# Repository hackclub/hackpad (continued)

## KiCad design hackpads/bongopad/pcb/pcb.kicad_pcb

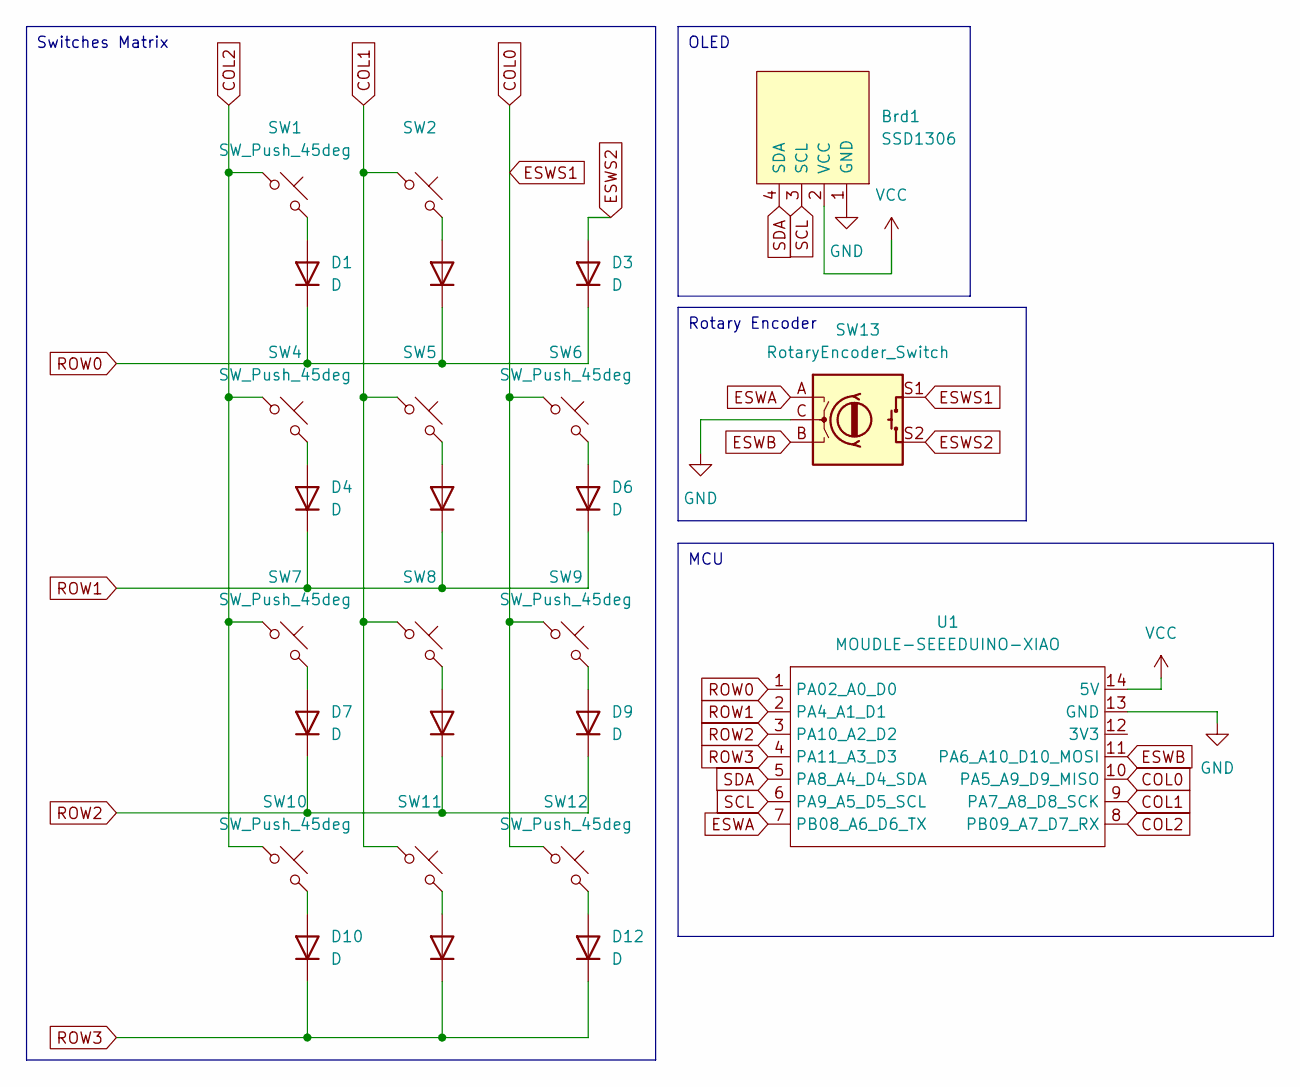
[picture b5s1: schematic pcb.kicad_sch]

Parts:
Brd1: SSD1306; 128x64OLED
D1, D2, D3, D4, D5, D6, D7, D8, D9, D10, D11, D12: D; D_DO-35_SOD27_P7.62mm_Horizontal
SW1, SW2, SW4, SW5, SW6, SW7, SW8, SW9, SW10, SW11, SW12: SW_Push_45deg; MX-Solderable-1U
SW13: RotaryEncoder_Switch; RotaryEncoder_Alps_EC11E-Switch_Vertical_H20mm
U1: MOUDLE-SEEEDUINO-XIAO; XIAO-Generic-Hybrid-14P-2.54-21X17.8MM

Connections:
COL0: SW6.1, SW9.1, SW12.1, SW13.S1, U1.10 (PA5_A9_D9_MISO)
COL1: SW2.1, SW5.1, SW8.1, SW11.1, U1.9 (PA7_A8_D8_SCK)
COL2: SW1.1, SW4.1, SW7.1, SW10.1, U1.8 (PB09_A7_D7_RX)
ESWA: SW13.A, U1.7 (PB08_A6_D6_TX)
ESWB: SW13.B, U1.11 (PA6_A10_D10_MOSI)
ESWS2: D3.2 (A), SW13.S2
GND: Brd1.1 (GND), SW13.C, U1.13 (GND)
unnamed: D1.2 (A), SW1.2
unnamed: D2.2 (A), SW2.2
unnamed: D4.2 (A), SW4.2
unnamed: D5.2 (A), SW5.2
unnamed: D6.2 (A), SW6.2
unnamed: D7.2 (A), SW7.2
unnamed: D8.2 (A), SW8.2
unnamed: D9.2 (A), SW9.2
unnamed: D10.2 (A), SW10.2
unnamed: D11.2 (A), SW11.2
unnamed: D12.2 (A), SW12.2
ROW0: D1.1 (K), D2.1 (K), D3.1 (K), U1.1 (PA02_A0_D0)
ROW1: D4.1 (K), D5.1 (K), D6.1 (K), U1.2 (PA4_A1_D1)
ROW2: D7.1 (K), D8.1 (K), D9.1 (K), U1.3 (PA10_A2_D2)
ROW3: D10.1 (K), D11.1 (K), D12.1 (K), U1.4 (PA11_A3_D3)
SCL: Brd1.3 (SCL), U1.6 (PA9_A5_D5_SCL)
SDA: Brd1.4 (SDA), U1.5 (PA8_A4_D4_SDA)
VCC: Brd1.2 (VCC), U1.14 (5V)

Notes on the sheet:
MCU
Switches Matrix
OLED
Rotary Encoder

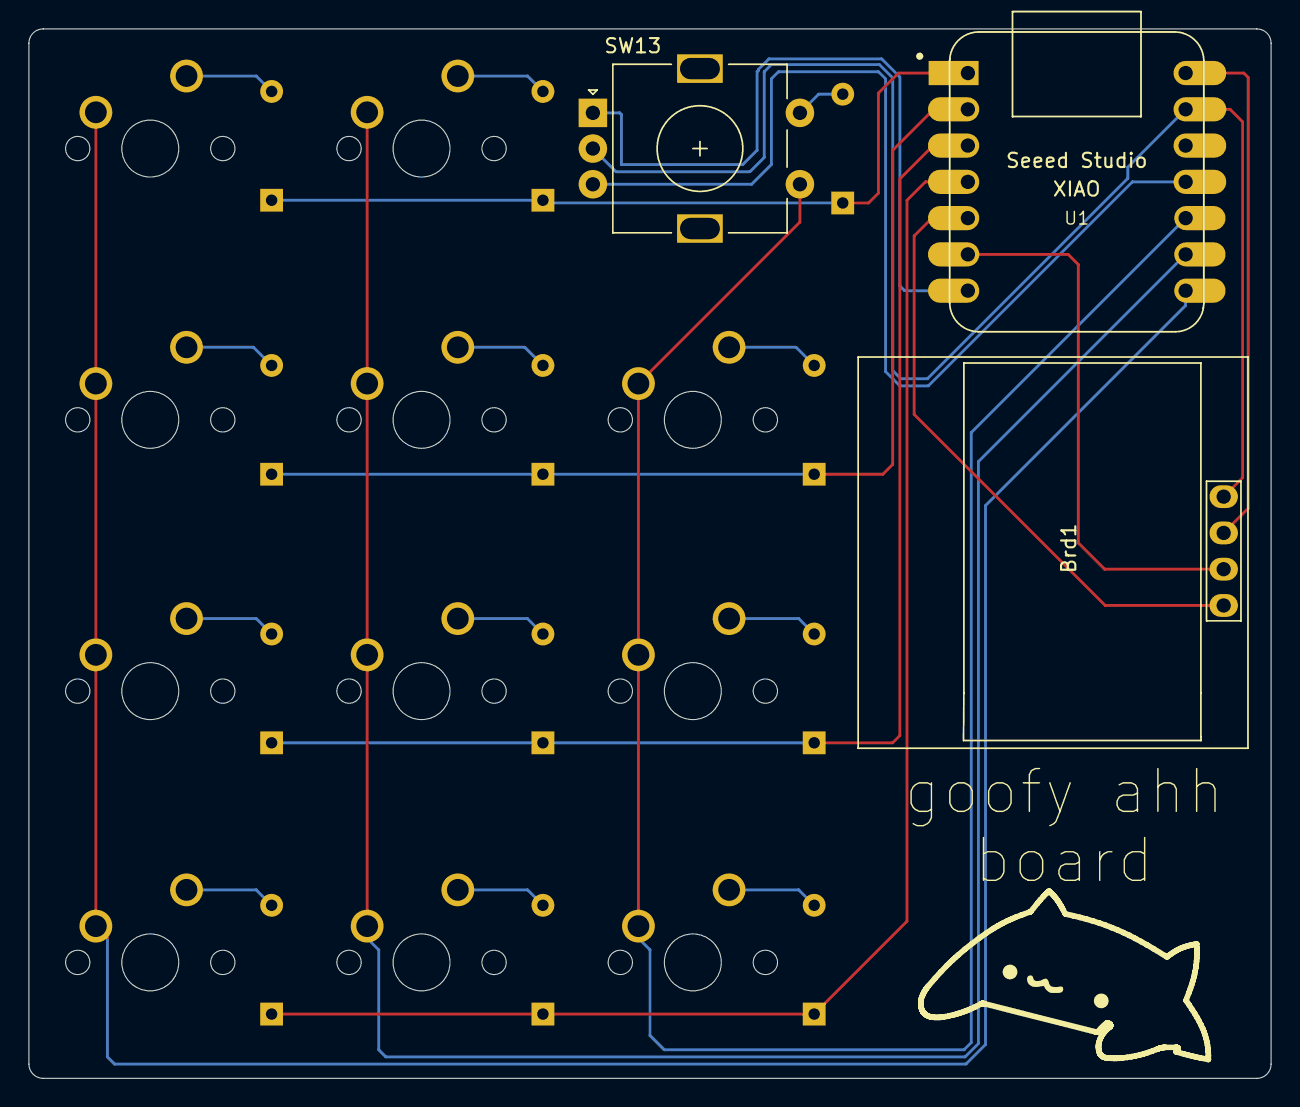
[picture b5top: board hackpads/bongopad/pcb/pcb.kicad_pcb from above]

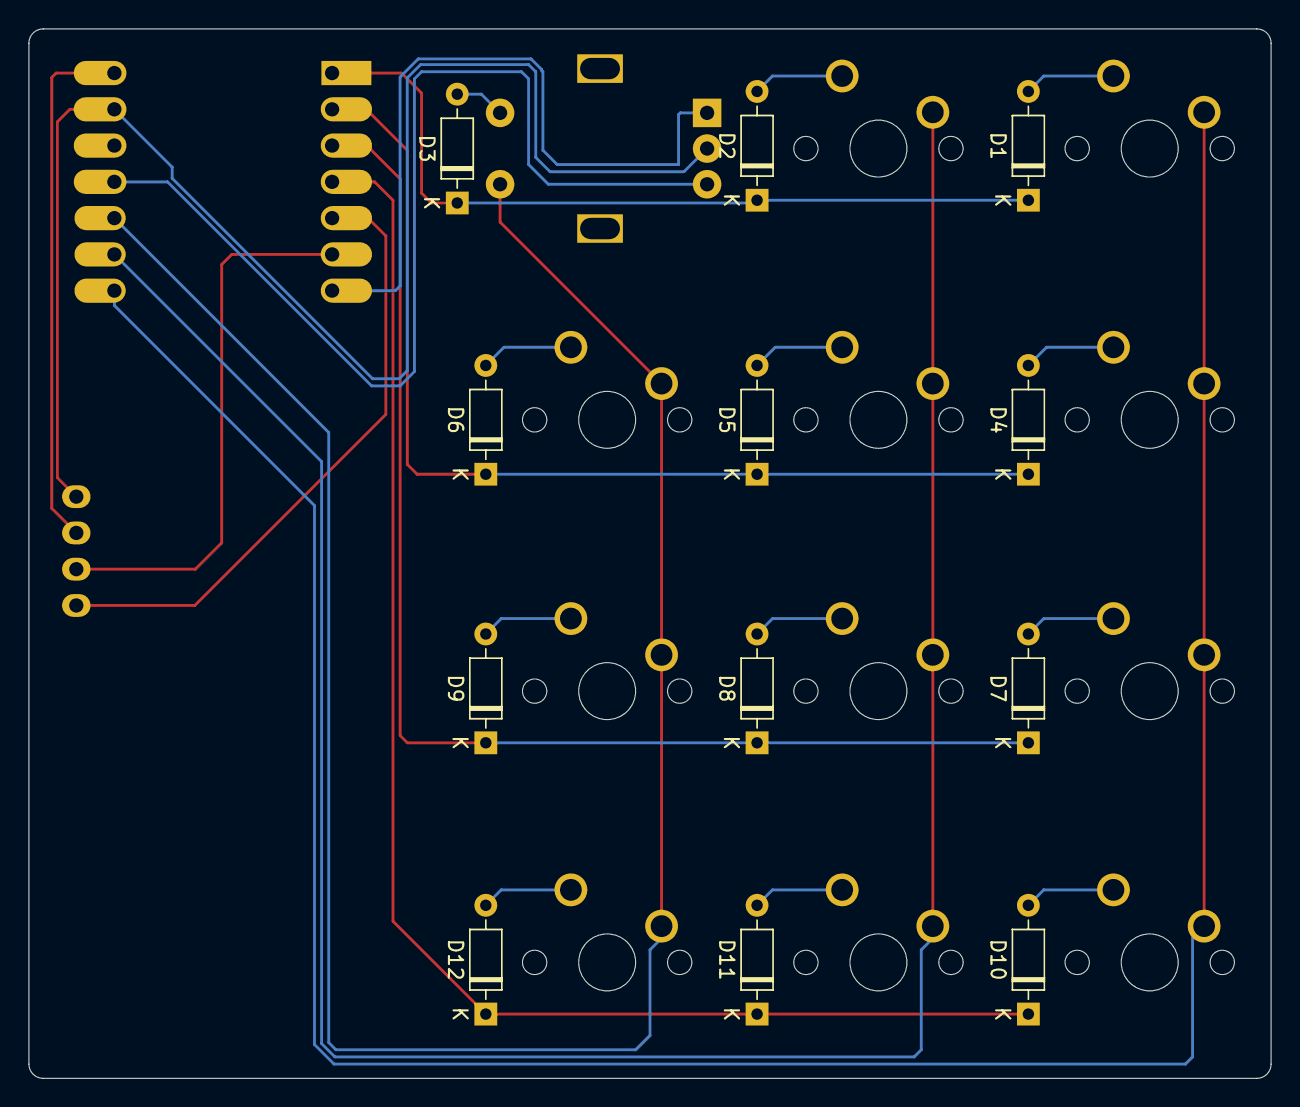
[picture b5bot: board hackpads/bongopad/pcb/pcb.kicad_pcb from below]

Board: 2 copper layers, 87.0 x 73.5 mm, 26 parts (12 on the bottom side), 25 nets.

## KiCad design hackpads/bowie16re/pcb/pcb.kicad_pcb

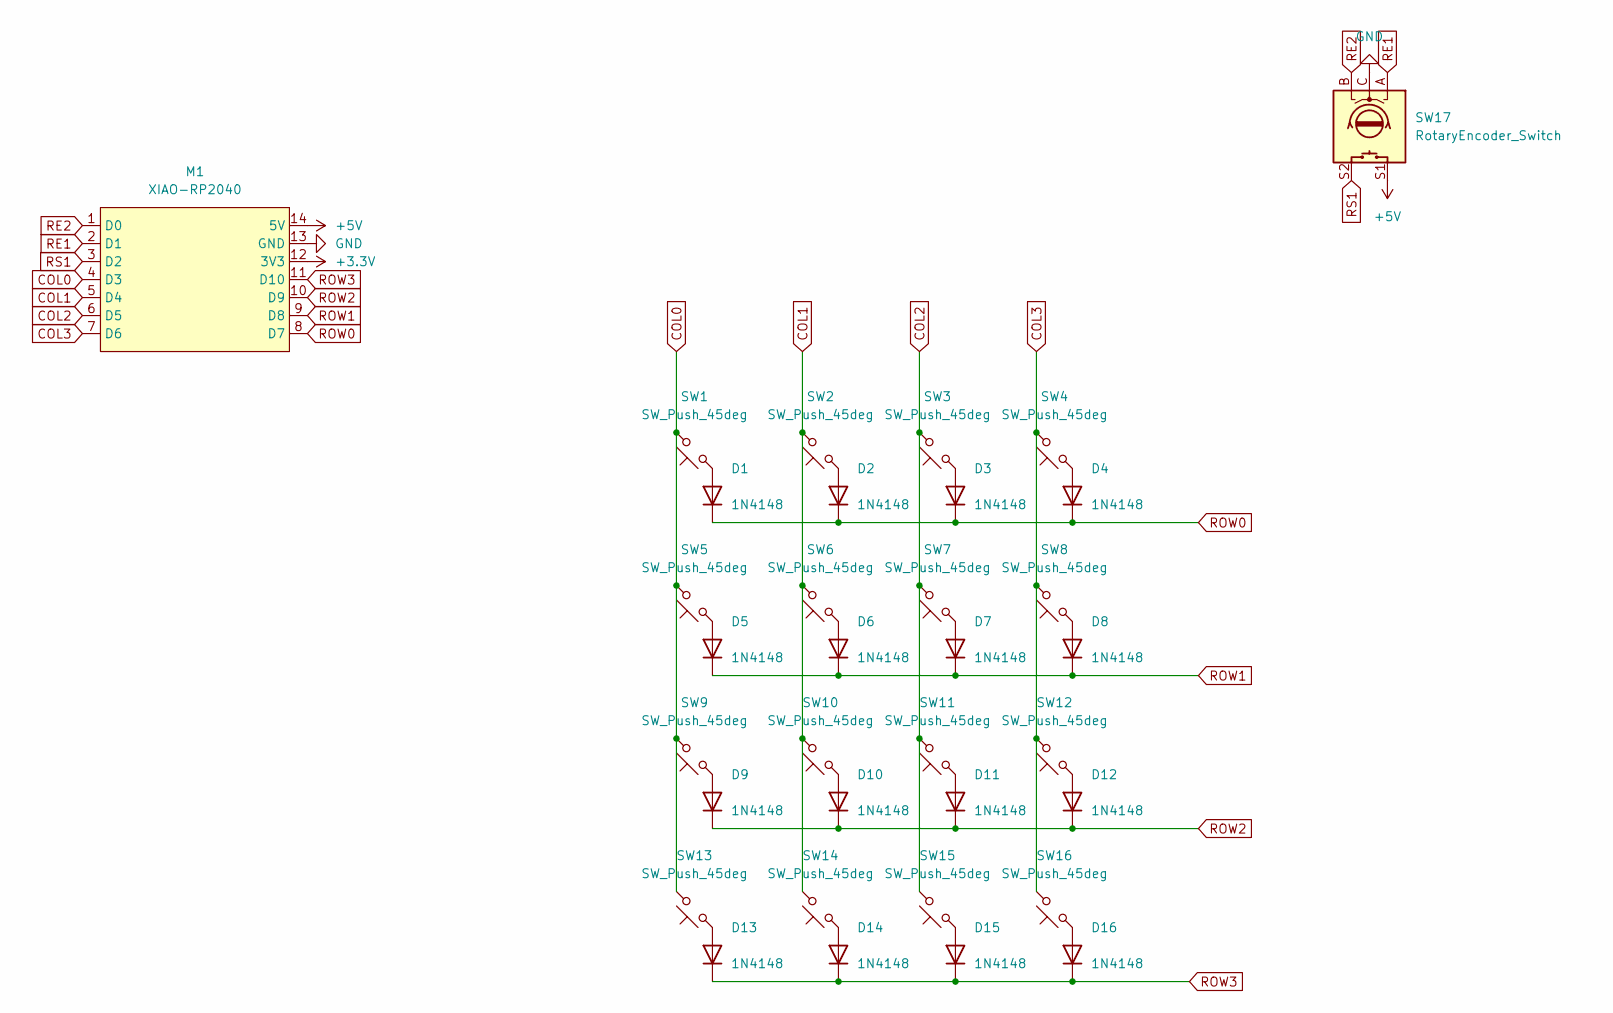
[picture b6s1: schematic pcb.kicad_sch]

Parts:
D1, D2, D3, D4, D5, D6, D7, D8, D9, D10, D11, D12, D13, D14, D15, D16: 1N4148; D_DO-35_SOD27_P7.62mm_Horizontal
M1: XIAO-RP2040
SW1, SW2, SW3, SW4, SW5, SW6, SW7, SW8, SW9, SW10, SW11, SW12, SW13, SW14, SW15, SW16: SW_Push_45deg; SW_Cherry_MX_1.00u_PCB
SW17: RotaryEncoder_Switch; RotaryEncoder_Alps_EC11E-Switch_Vertical_H20mm

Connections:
+3.3V: M1.12 (3V3)
+5V: M1.14 (5V), SW17.S1
COL0: M1.4 (D3), SW1.2, SW5.2, SW9.2, SW13.2
COL1: M1.5 (D4), SW2.2, SW6.2, SW10.2, SW14.2
COL2: M1.6 (D5), SW3.2, SW7.2, SW11.2, SW15.2
COL3: M1.7 (D6), SW4.2, SW8.2, SW12.2, SW16.2
GND: M1.13 (GND), SW17.C
unnamed: D1.2 (A), SW1.1
unnamed: D2.2 (A), SW2.1
unnamed: D3.2 (A), SW3.1
unnamed: D4.2 (A), SW4.1
unnamed: D5.2 (A), SW5.1
unnamed: D6.2 (A), SW6.1
unnamed: D7.2 (A), SW7.1
unnamed: D8.2 (A), SW8.1
unnamed: D9.2 (A), SW9.1
unnamed: D10.2 (A), SW10.1
unnamed: D11.2 (A), SW11.1
unnamed: D12.2 (A), SW12.1
unnamed: D13.2 (A), SW13.1
unnamed: D14.2 (A), SW14.1
unnamed: D15.2 (A), SW15.1
unnamed: D16.2 (A), SW16.1
RE1: M1.2 (D1), SW17.A
RE2: M1.1 (D0), SW17.B
ROW0: D1.1 (K), D2.1 (K), D3.1 (K), D4.1 (K), M1.8 (D7)
ROW1: D5.1 (K), D6.1 (K), D7.1 (K), D8.1 (K), M1.9 (D8)
ROW2: D9.1 (K), D10.1 (K), D11.1 (K), D12.1 (K), M1.10 (D9)
ROW3: D13.1 (K), D14.1 (K), D15.1 (K), D16.1 (K), M1.11 (D10)
RS1: M1.3 (D2), SW17.S2

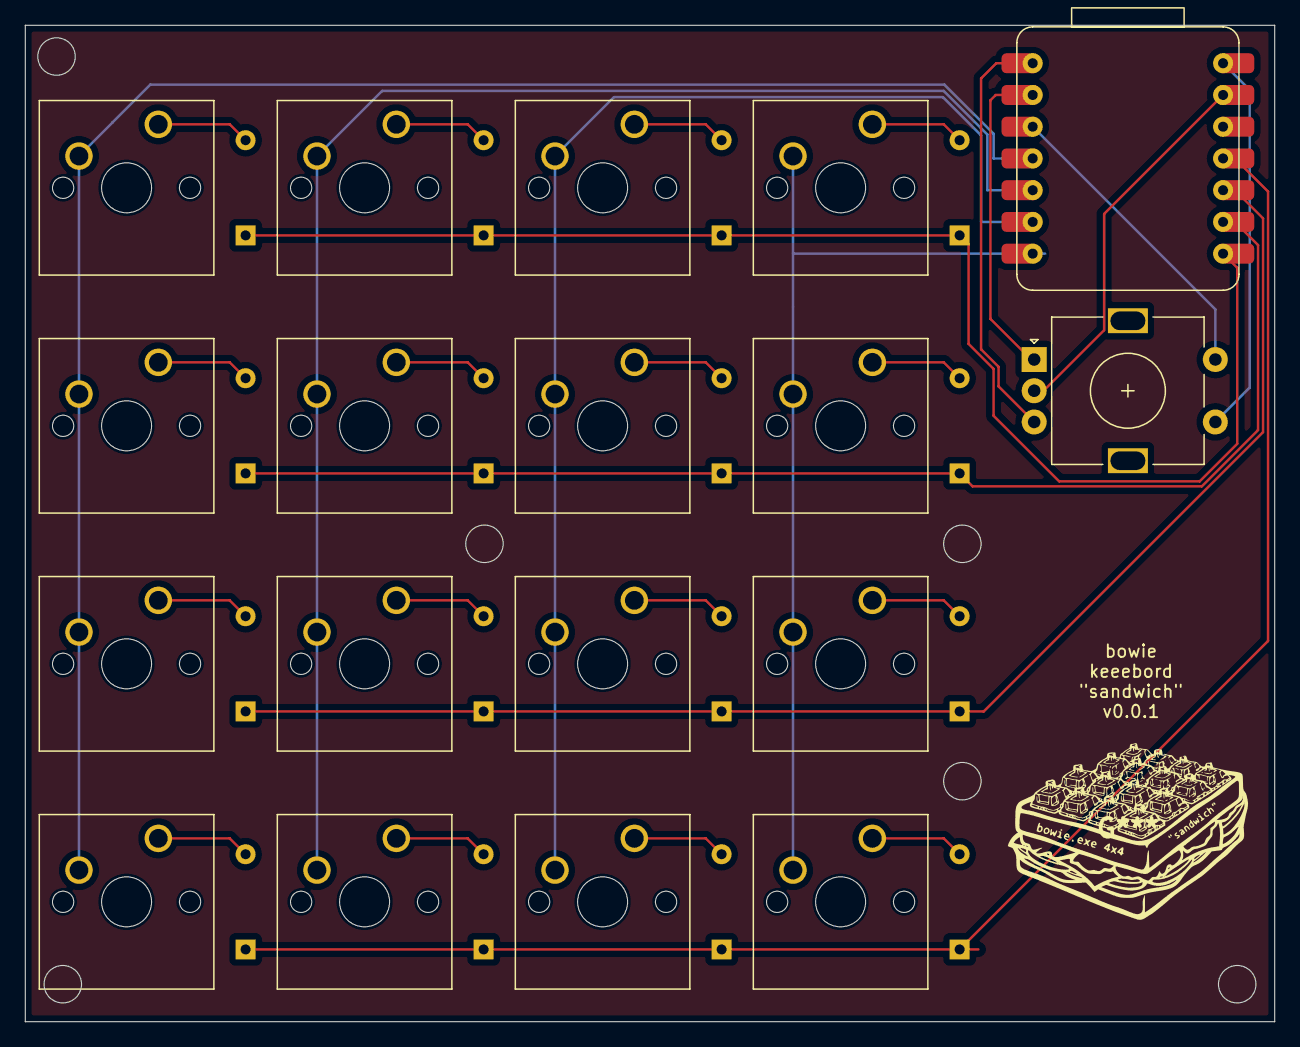
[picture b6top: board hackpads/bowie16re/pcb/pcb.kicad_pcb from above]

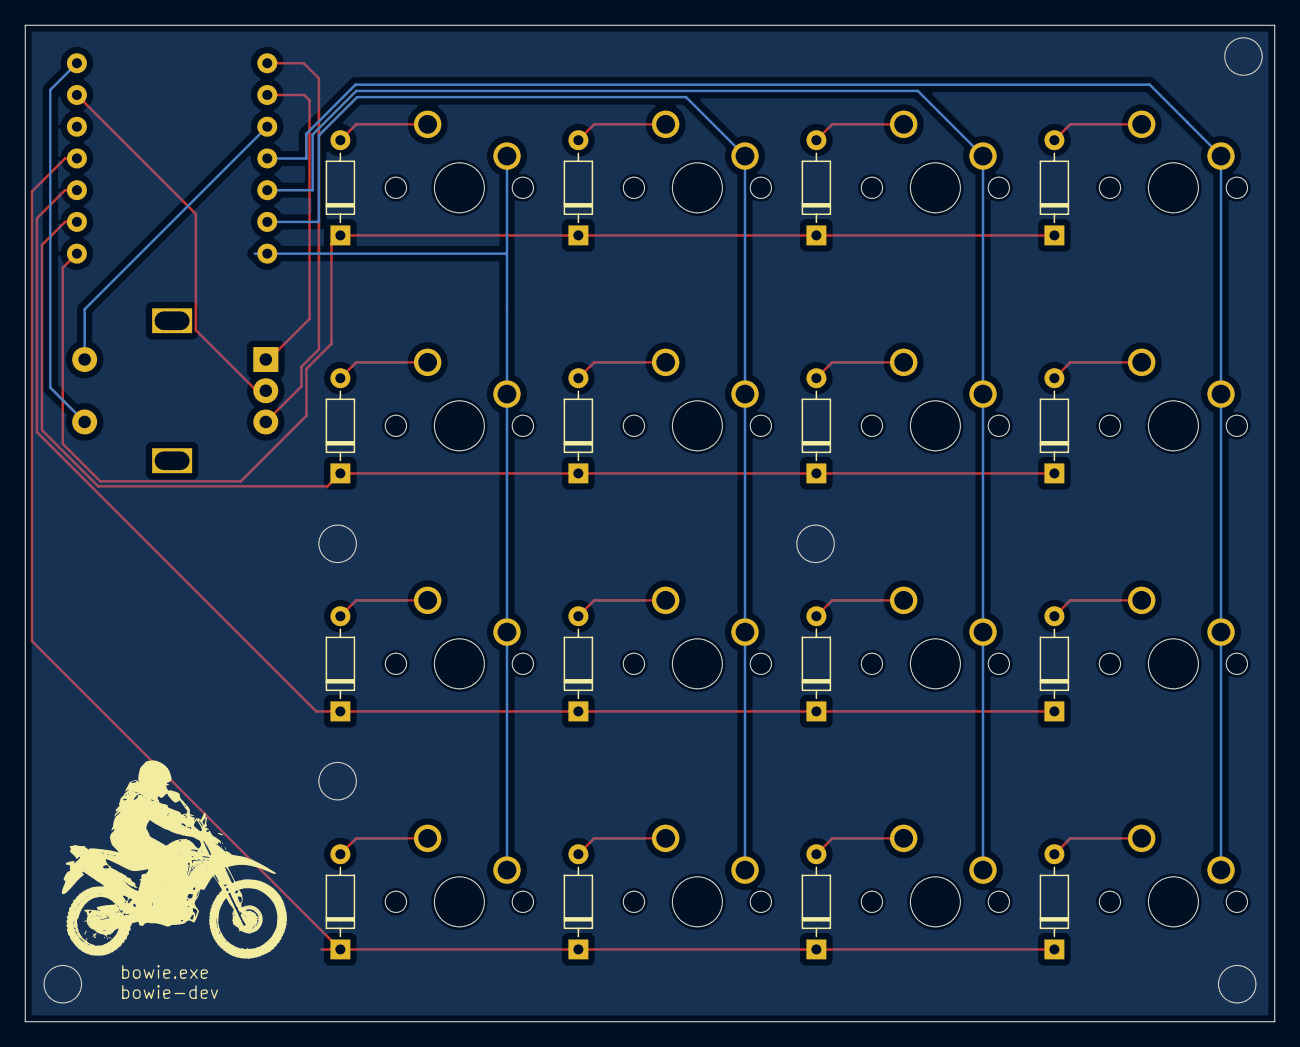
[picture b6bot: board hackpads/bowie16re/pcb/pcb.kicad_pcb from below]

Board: 2 copper layers, 100.0 x 79.8 mm, 34 parts (16 on the bottom side), 29 nets.
